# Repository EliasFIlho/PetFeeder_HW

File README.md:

# PetFeeder_HW

## V1 Board for my Pet Feeder project

## [Software Repository](https://github.com/EliasFIlho/Automatic_pet_feeder)

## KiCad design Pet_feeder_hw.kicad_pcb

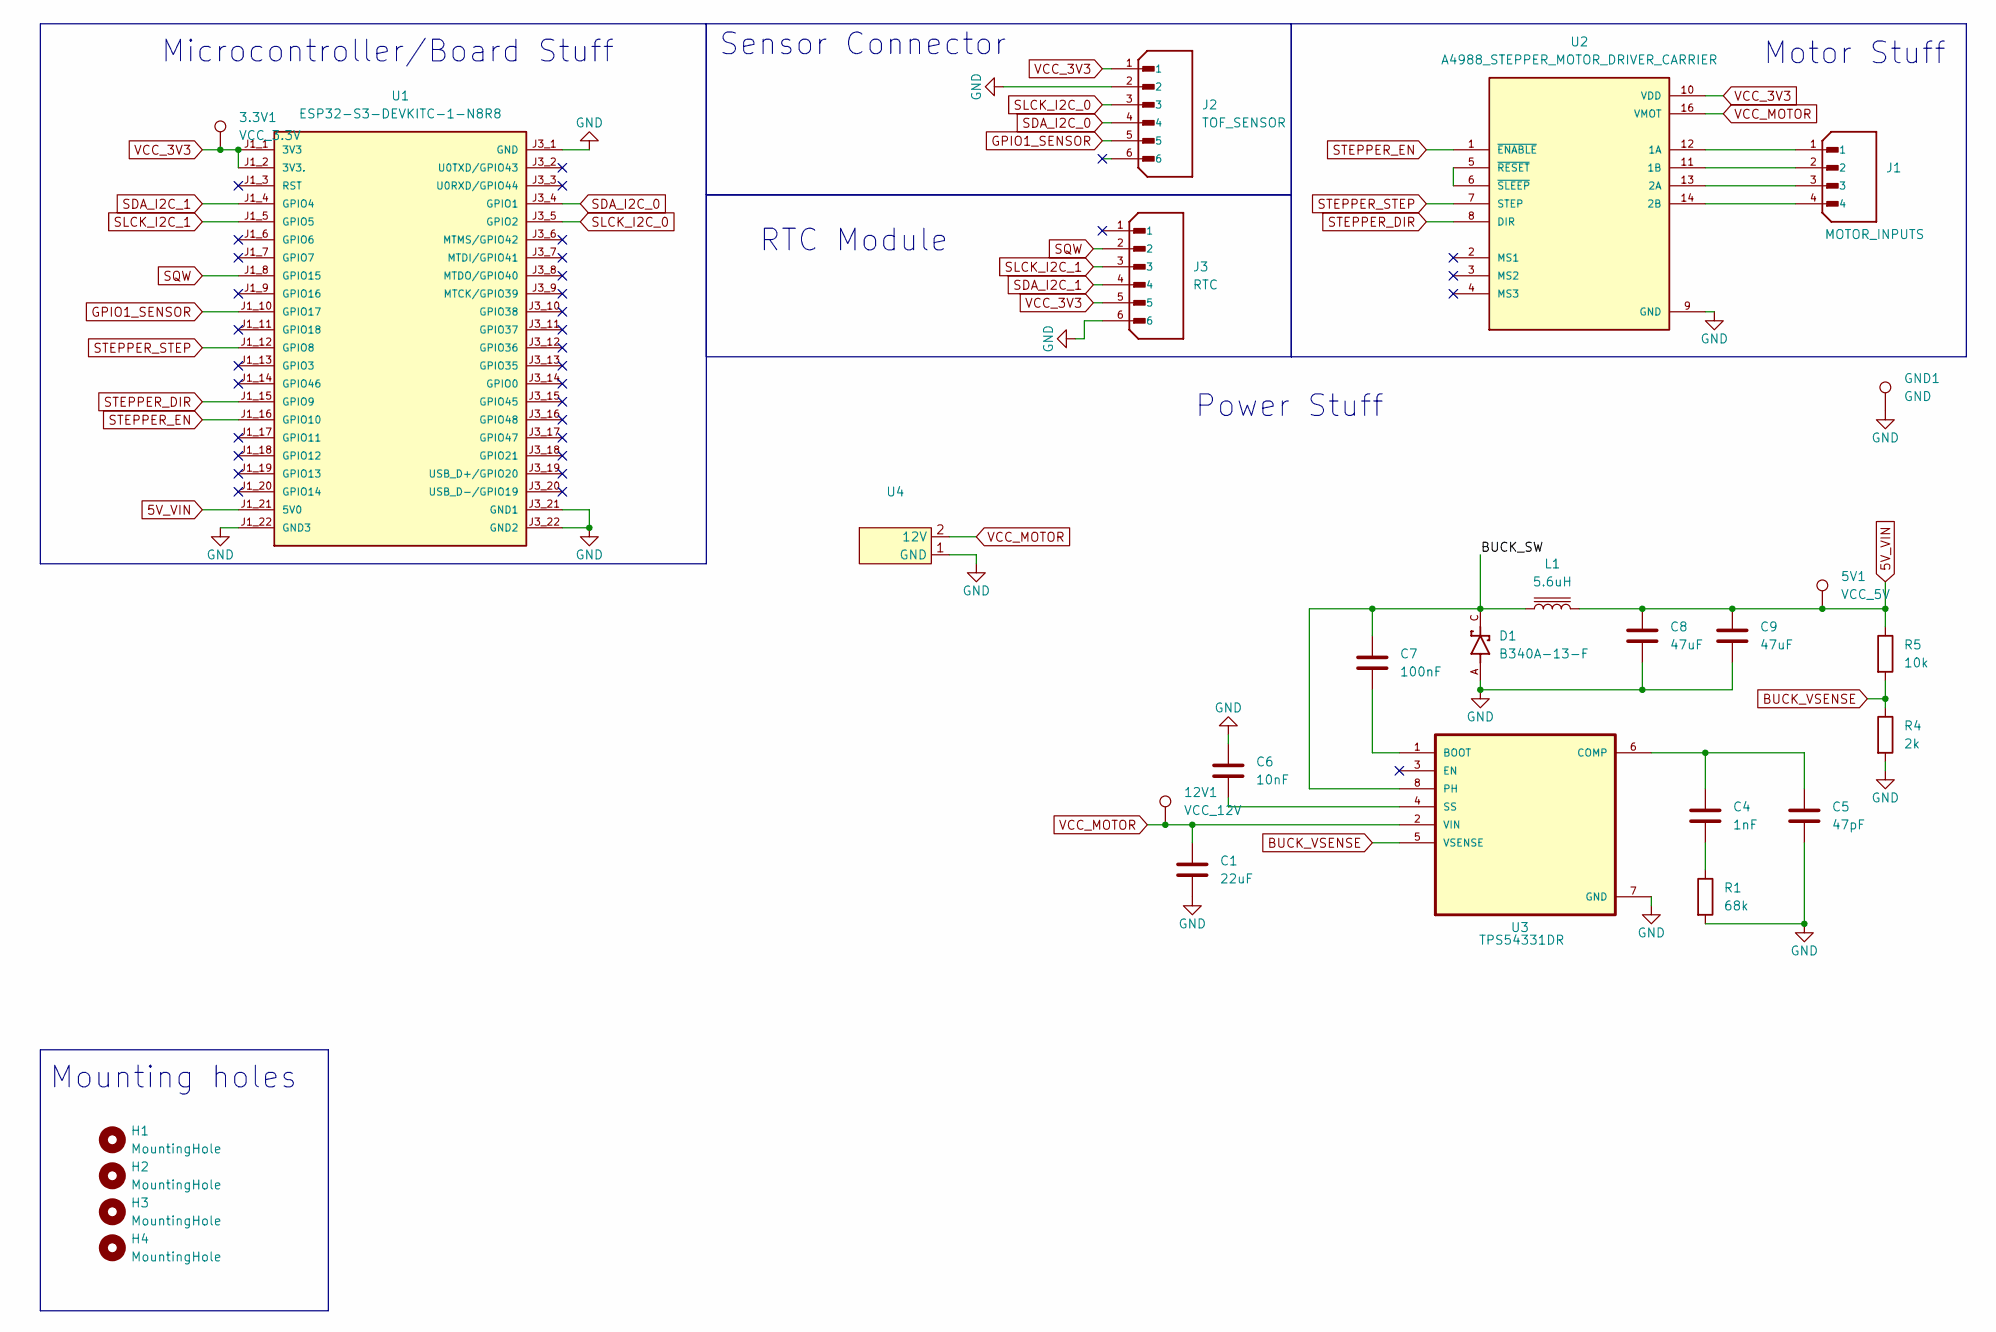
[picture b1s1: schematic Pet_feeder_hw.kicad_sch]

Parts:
3.3V1: VCC_3.3V; TestPoint_Pad_D2.0mm
5V1: VCC_5V; TestPoint_Pad_D2.0mm
12V1: VCC_12V; TestPoint_Pad_D2.0mm
C1: 22uF; C_0805_2012Metric; JLCPCB Part # C45783
C4: 1nF; C_0805_2012Metric; JLCPCB Part # C46653
C5: 47pF; C_0805_2012Metric; JLCPCB Part # C14857
C6: 10nF; C_0805_2012Metric; JLCPCB Part # C1710
C7: 100nF; C_0805_2012Metric; JLCPCB Part # C28233
C8, C9: 47uF; C_0805_2012Metric; JLCPCB Part # C16780
D1: B340A-13-F; DIOM5226X240N; PARTREV 17-2; JLCPCB Part # C64982
GND1: GND; TestPoint_Pad_D2.0mm
H1, H2, H3, H4: MountingHole; MountingHole_2.1mm
J1: MOTOR_INPUTS; JST_B4B-XH-A; PARTREV 7/4/21; JLCPCB Part # C144395
J2: TOF_SENSOR; JST_B6B-XH-A; PARTREV 7/4/21; JLCPCB Part # C144397
J3: RTC; JST_B6B-XH-A; PARTREV 7/4/21; JLCPCB Part # C144397
L1: 5.6uH; IND_XAL4030-682MEC; JLCPCB Part # C3040663
R1: 68k; R_0805_2012Metric; LCSC Part # C17801
R4: 2k; R_0805_2012Metric; JLCPCB Part # C17604
R5: 10k; R_0805_2012Metric; JLCPCB Part # C17414
U1: ESP32-S3-DEVKITC-1-N8R8
U2: A4988_STEPPER_MOTOR_DRIVER_CARRIER; MODULE_A4988_STEPPER_MOTOR_DRIVER_CARRIER
U3: TPS54331DR; SOIC127P599X175-8N; JLCPCB Part # C9865
U4: USB_BOARD

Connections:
5V_VIN: 5V1.1, C8.1, C9.1, L1.2, R5.1, U1.J1_21 (5V0)
/BUCK_SW: C7.1, D1.C, L1.1, U3.8 (PH)
BUCK_VSENSE: R4.1, R5.2, U3.5 (VSENSE)
GND: C1.2, C5.2, C6.1, C8.2, C9.2, D1.A, GND1.1, J2.2, J3.6, R1.2, R4.2, U1.J1_22 (GND3), U1.J3_1 (GND), U1.J3_21 (GND1), U1.J3_22 (GND2), U2.9 (GND), U2.15 (GND), U3.7 (GND), U4.1 (GND)
GPIO1_SENSOR: J2.5, U1.J1_10 (GPIO17)
unnamed: C4.2, R1.1
unnamed: J1.1, U2.12 (1A)
unnamed: J1.2, U2.11 (1B)
unnamed: J1.3, U2.13 (2A)
unnamed: J1.4, U2.14 (2B)
unnamed: U2.5 (~RESET), U2.6 (~SLEEP)
unnamed: C7.2, U3.1 (BOOT)
unnamed: C4.1, C5.1, U3.6 (COMP)
unnamed: C6.2, U3.4 (SS)
SDA_I2C_0: J2.4, U1.J3_4 (GPIO1)
SDA_I2C_1: J3.4, U1.J1_4 (GPIO4)
SLCK_I2C_0: J2.3, U1.J3_5 (GPIO2)
SLCK_I2C_1: J3.3, U1.J1_5 (GPIO5)
SQW: J3.2, U1.J1_8 (GPIO15)
STEPPER_DIR: U1.J1_15 (GPIO9), U2.8 (DIR)
STEPPER_EN: U1.J1_16 (GPIO10), U2.1 (~ENABLE)
STEPPER_STEP: U1.J1_12 (GPIO8), U2.7 (STEP)
VCC_3V3: 3.3V1.1, J2.1, J3.5, U1.J1_1 (3V3), U1.J1_2 (3V3.), U2.10 (VDD)
VCC_MOTOR: 12V1.1, C1.1, U2.16 (VMOT), U3.2 (VIN), U4.2 (12V)

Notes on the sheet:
RTC Module
Mounting holes
Motor Stuff
Sensor Connector
Power Stuff
Microcontroller/Board Stuff

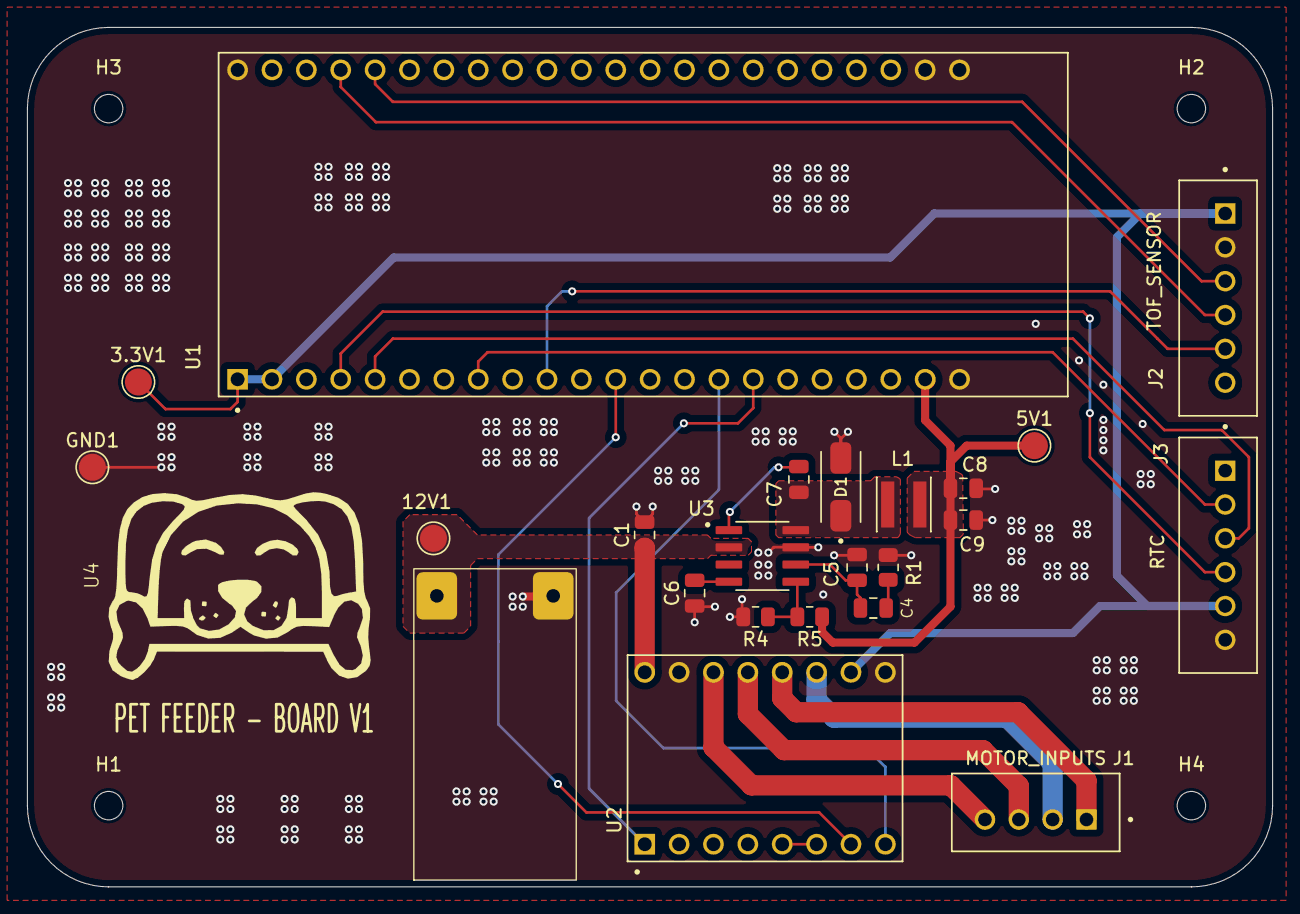
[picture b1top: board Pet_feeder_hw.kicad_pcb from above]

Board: 2 copper layers, 92.0 x 63.5 mm, 27 parts (0 on the bottom side), 24 nets.

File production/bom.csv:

Designator,Footprint,Quantity,Value,LCSC Part #
12V1,TestPoint_Pad_D2.0mm,1,VCC_12V,
3.3V1,TestPoint_Pad_D2.0mm,1,VCC_3.3V,
5V1,TestPoint_Pad_D2.0mm,1,VCC_5V,
C1,0805,1,22uF,C45783
C4,0805,1,1nF,C46653
C5,0805,1,47pF,C14857
C6,0805,1,10nF,C1710
C7,0805,1,100nF,C28233
"C8, C9",0805,2,47uF,C16780
D1,DIOM5226X240N,1,B340A-13-F,C64982
GND1,TestPoint_Pad_D2.0mm,1,GND,
J1,JST_B4B-XH-A,1,MOTOR_INPUTS,C144395
J2,JST_B6B-XH-A,1,TOF_SENSOR,C144397
J3,JST_B6B-XH-A,1,RTC,C144397
L1,IND_XAL4030-682MEC,1,5.6uH,C3040663
R1,0805,1,68k,C17801
R4,0805,1,2k,C17604 
R5,0805,1,10k,C17414
U1,ESP32-S3-DEVKITC-1-N8R8,1,ESP32-S3-DEVKITC-1-N8R8,
U2,MODULE_A4988_STEPPER_MOTOR_DRIVER_CARRIER,1,A4988_STEPPER_MOTOR_DRIVER_CARRIER,
U3,SOIC127P599X175-8N,1,TPS54331DR,C9865
U4,USB_BOARD,1,~,

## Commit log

2026-04-30 Added link for software repo on README
